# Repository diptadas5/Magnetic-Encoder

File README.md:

# Magnetic-Encoder
--------------------------------------------------------------------------------------------------------------------------------------------------------------------------------
 
* Designed an encoder that detects the position of a magnet and converts it's motion into an analog / digital output signal.
* The position data is read on an Arduino. 
* This board uses a AS5047P encoder chip along with other relevant circuit components.
* The purpose of making this board is to reduce retail price. One of these boards sell for $24.22 from supplier.
* Creating this board from scratch and implementing panelization saved $147 on one bacth of order (20 boards).

# Manufacturing Process
--------------------------------------------------------------------------------------------------------------------------------------------------------------------------------

* First we meet client's board specifications. This board already had the circuitry set up according to the supplier. Only specification was to panelize the board.
* Therefore we first draw the schematic of the board.

* Once we are done drawing the schematic, it's time to lay out a floorplan for the physical board.

* One of our specification was to panelize the board. The following is the floorplan after panelization 

* The manufacture's prototype is included below.

# Finished Product
--------------------------------------------------------------------------------------------------------------------------------------------------------------------------------
* Once we were done, we downloaded the Eagle gerber files and uploaded them onto the manufacterer's website to order them. Below are some images of the physical board and the board in use.

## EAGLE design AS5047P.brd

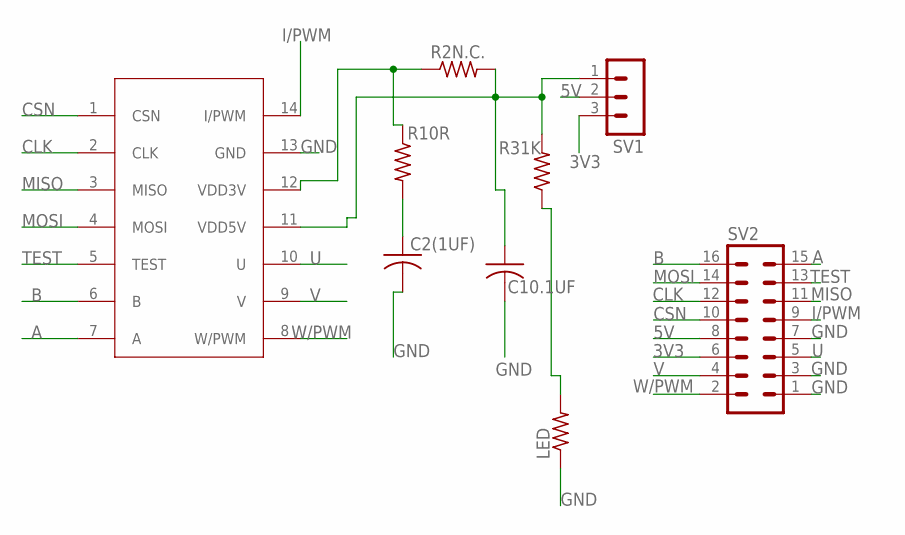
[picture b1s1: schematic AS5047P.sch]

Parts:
C2(1UF), C10.1UF: C-USC1206; C1206
LED: R-US_R1206; R1206
R2N.C., R10R, R31K: R-US_R1206; R1206
SV1: MA03-1
SV2: MA08-2
U$1: AS5047; SOP65P640X110-14N

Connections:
3V3: SV1.3, SV2.6
5V: SV1.2, SV2.8
A: SV2.15, U$1.7 (A)
B: SV2.16, U$1.6 (B)
CLK: SV2.12, U$1.2 (CLK)
CSN: SV2.10, U$1.1 (CSN)
GND: C2(1UF).2, C10.1UF.2, LED.1, SV2.1, SV2.3, SV2.7, U$1.13 (GND)
I/PWM: SV2.9, U$1.14 (I/PWM)
MISO: SV2.11, U$1.3 (MISO)
MOSI: SV2.14, U$1.4 (MOSI)
unnamed: R2N.C..1, R10R.1, U$1.12 (VDD3V)
unnamed: LED.2, R31K.1
unnamed: C2(1UF).1, R10R.2
unnamed: C10.1UF.1, R2N.C..2, R31K.2, SV1.1, U$1.11 (VDD5V)
TEST: SV2.13, U$1.5 (TEST)
U: SV2.5, U$1.10 (U)
V: SV2.4, U$1.9 (V)
W/PWM: SV2.2, U$1.8 (W/PWM)

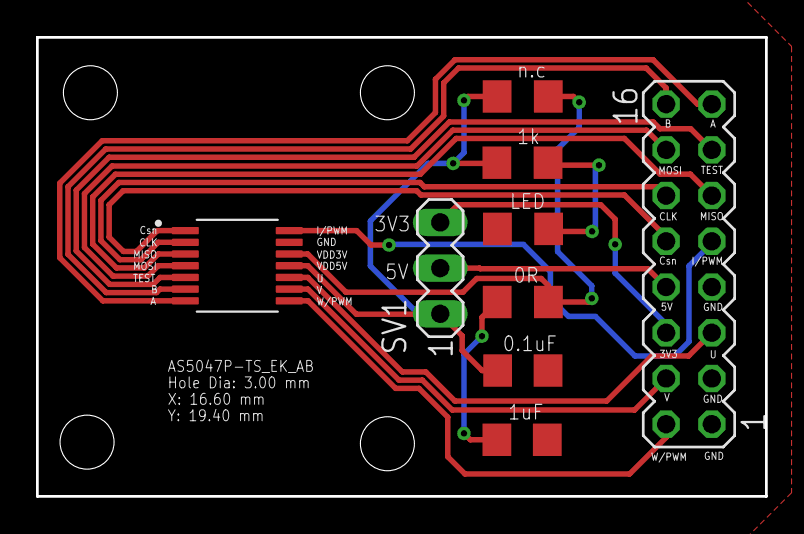
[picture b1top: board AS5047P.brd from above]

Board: 2 copper layers, 40.5 x 25.5 mm, 9 parts (0 on the bottom side), 18 nets.

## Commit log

2020-10-19 Magnetic Encoder
